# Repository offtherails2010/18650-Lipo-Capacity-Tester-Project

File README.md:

# 18650-Lipo-Capacity-Tester-Project
18650/Lipo Capacity Tester for any Li-ion 3.6v to 4.35v Cells to find the 'True' mAh Rating &amp; 
Display Results on a Nokia 5110 LCD Screen

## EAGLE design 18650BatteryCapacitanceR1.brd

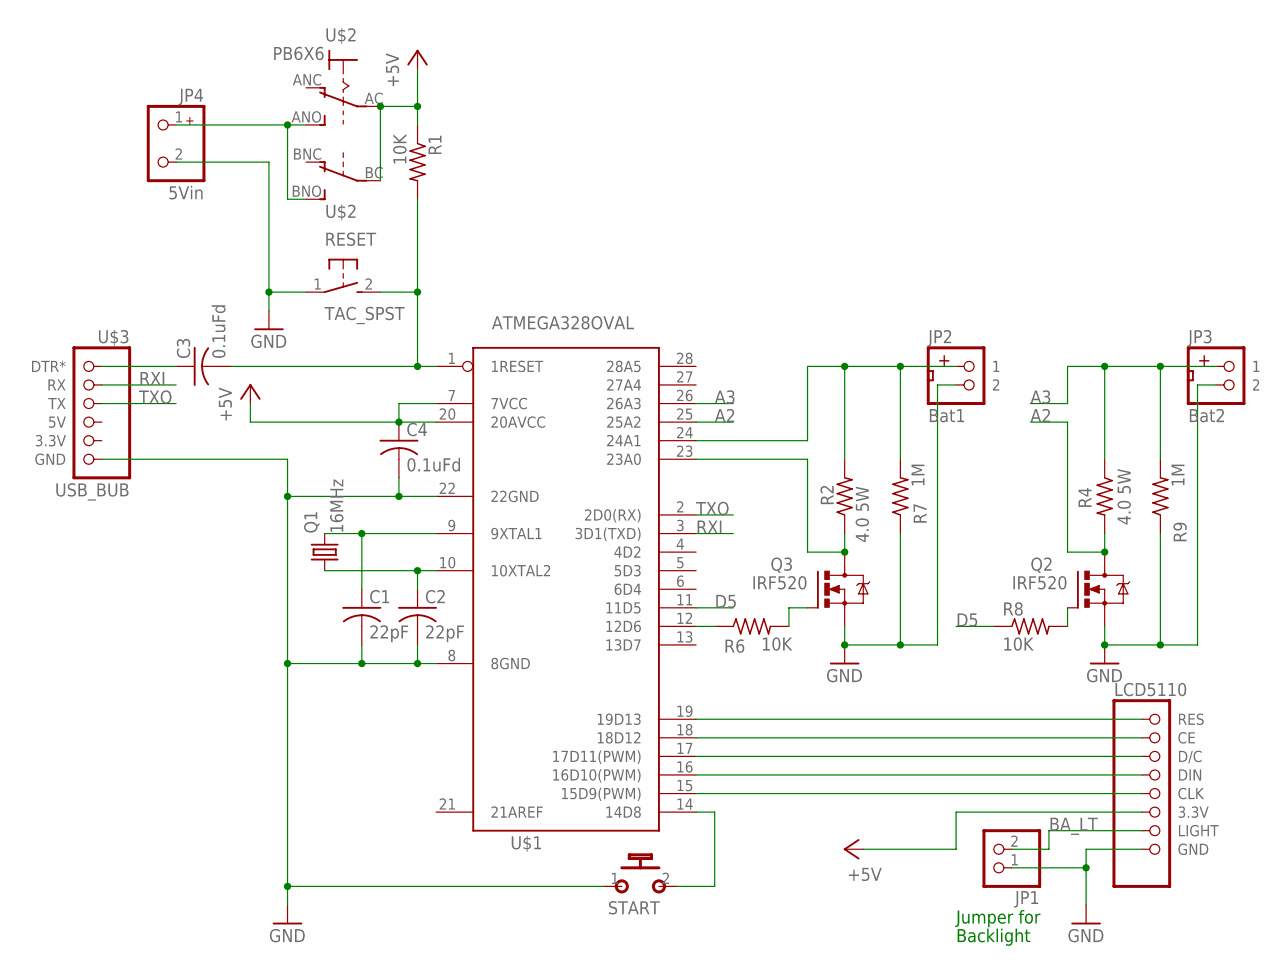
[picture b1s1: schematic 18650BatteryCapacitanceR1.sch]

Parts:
C1, C2: 22pF; C025-025X050
C3: 0.1uFd; C075-032X103
C4: 0.1uFd; C025-025X050
JP1: PINHD-1X2; 1X02
JP2: Bat1; JST2.0
JP3: Bat2; JST2.0
JP4: 5Vin; KF301
LCD5110: LCD5110_1TOP; LCD5110T1
Q1: 16MHz; HC49/S
Q2, Q3: IRF520; TO220BV
R1, R6, R8: 10K; 0207/7
R2, R4: 4.0 5W; 0922/22
R7, R9: 1M; 0207/2V
RESET: TAC_SPST; TACTILE-SPST
START: MOMENTARY; SPST
U$1: ATMEGA328OVAL; DIL28-3
U$2: PB6X6
U$3: USB_BUB

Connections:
+5V: C4.1, LCD5110.3.3V, R1.1, U$1.7 (7VCC), U$1.20 (20AVCC), U$2.AC, U$2.BC
A2: Q2.D, R4.2, U$1.25 (25A2)
A3: JP3.1, R4.1, R9.2, U$1.26 (26A3)
BA_LT: JP1.2, LCD5110.LIGHT
D5: R8.1, U$1.11 (11D5)
GND: C1.2, C2.2, C4.2, JP1.1, JP2.2, JP3.2, JP4.2, LCD5110.GND, Q2.S, Q3.S, R7.1, R9.1, RESET.1, START.1, U$1.8 (8GND), U$1.22 (22GND), U$3.GND
unnamed: C1.1, Q1.2, U$1.9 (9XTAL1)
unnamed: C2.1, Q1.1, U$1.10 (10XTAL2)
unnamed: JP4.1, U$2.ANO (S), U$2.BNO (S)
unnamed: START.2 (S), U$1.14 (14D8)
unnamed: C3.2, R1.2, RESET.2, U$1.1 (1RESET)
unnamed: C3.1, U$3.DTR*
unnamed: Q2.G, R8.2
unnamed: LCD5110.RES, U$1.19 (19D13)
unnamed: LCD5110.CE, U$1.18 (18D12)
unnamed: LCD5110.D/C, U$1.17 (17D11(PWM))
unnamed: LCD5110.DIN, U$1.16 (16D10(PWM))
unnamed: LCD5110.CLK, U$1.15 (15D9(PWM))
unnamed: R6.1, U$1.12 (12D6)
unnamed: Q3.G, R6.2
unnamed: Q3.D, R2.1, U$1.23 (23A0)
unnamed: JP2.1, R2.2, R7.2, U$1.24 (24A1)
RXI: U$1.3 (3D1(TXD)), U$3.RX
TXO: U$1.2 (2D0(RX)), U$3.TX

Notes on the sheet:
Jumper for
Backlight

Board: 2 copper layers, 24 parts (0 on the bottom side), 24 nets, no tracks yet.

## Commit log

2017-07-26 Create LICENSE
2017-07-26 Set theme jekyll-theme-midnight
2017-07-26 Update LICENSE
